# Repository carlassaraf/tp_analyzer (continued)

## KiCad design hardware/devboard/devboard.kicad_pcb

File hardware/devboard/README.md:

# RP2350B Development Board

**Rev 1** — 2026-08-18 · Fabrizio Carlassara · UTN FRA, Departamento de Ingeniería Electrónica, Cátedra de Proyecto Final

KiCad project: [`devboard.kicad_pro`](devboard.kicad_pro) · Schematic: [`devboard.kicad_sch`](devboard.kicad_sch) · PCB: [`devboard.kicad_pcb`](devboard.kicad_pcb)

## Overview

A minimal development/breakout board built around the **[Core2350B0](https://www.waveshare.com/wiki/Core2350B0)** module (an RP2350B‑QFN80 SoM), with a parallel-interface **[3.5″ ILI9486 TFT + SD card shield](https://www.lcdwiki.com/3.5inch_Arduino_Display-UNO)**, a rotary encoder for UI input, 8 analog input headers, an I²C header, an SWD debug header, and a selectable power path that can run from USB, an external 5V source/boost module, or a Li‑Po/Li-ion battery.

- **Board:** 2-layer, 55.45 mm × 64.95 mm
- **MCU module:** U1 — [Core2350B0](https://www.waveshare.com/wiki/Core2350B0) (RP2350B in QFN-80), custom project symbol/footprint
- **Display:** U4 — [ILI9486 3.5″ TFT shield](https://www.lcdwiki.com/3.5inch_Arduino_Display-UNO) (8-bit parallel/8080 interface) with onboard microSD slot (SPI)
- **Power:** Li‑Po/Li‑ion input, USB VBUS, or external 5V/boost module → selectable VSYS → AMS1117-3.3 → +3V3
- **Input:** SW1 rotary encoder with integrated push-button

## Components

| Ref | Part | Function |
|---|---|---|
| U1 | [Core2350B0](https://www.waveshare.com/wiki/Core2350B0) (RP2350B QFN‑80) | Main MCU module |
| U2 | [AMS1117CD‑3.3](https://www.advanced-monolithic.com/pdf/ds1117.pdf) (SOT‑223) | Linear regulator, VSYS → +3V3 |
| U4 | [ILI9486 3.5″ TFT Shield](https://www.lcdwiki.com/3.5inch_Arduino_Display-UNO) | Display + resistive-touch‑shield form factor, 8-bit parallel LCD bus, onboard microSD (SPI) |
| U5 | 3-pin header, socket for [PCBoard.ca Mini Boost Converter 5V](https://www.pcboard.ca/mini-boost-converter-5v) | Plug-in step-up module, boosts VBAT (~3.7V Li‑Po) to a regulated +5V |
| SW1 | Rotary encoder w/ push switch | UI input — quadrature A/B + click |
| R1, R2, R3 | 10 kΩ (0805) | Pull-ups to +3V3 for encoder A, B, and switch lines |
| C1, C5 | 10 µF MLCC | Decoupling on VSYS and +3V3 |
| JP1 | 3-pin jumper (bridged 1‑2 by default) | VSYS power-source select: **+5V** (external header/boost module) vs **VBUS** (USB) |
| J4 | 3-pin header | SWD debug (SWCLK, GND, SWDIO) |
| J5 | 4-pin header | I²C breakout (+3V3, GPIO8, GPIO9, GND) |
| J6–J13 | 2-pin headers | ADC0–ADC7 analog input breakouts (signal + GND) |
| J14 | 2-pin header | Battery input (VBAT, GND) — single-cell Li‑Po/Li‑ion, no onboard charge management |

> ⚠️ U5 and J14 use generic 2.54 mm pin-header footprints as placeholders — U5 is a socket for the plug-in boost module linked above (not a fixed regulator IC on this PCB), and J14 is a bare 2-pin header rather than a JST-PH battery connector. J4 is likewise a standard 2.54 mm SWD header (a schematic note calls it a "JST Debug Connector", but no JST part is actually used).

## Power architecture

```
Battery (Li-Po/Li-ion, ~3.7V) ──► J14 ──► U5 (external boost module) ──► +5V ─┐
                                                                               ├─► JP1 ──► VSYS ──► U2 (AMS1117-3.3) ──► +3V3
                                       USB VBUS (from U1's onboard USB) ──────┘
```

- **JP1** selects what feeds VSYS: bridge pins **1-2** to power VSYS from the external **+5V** rail (boost module output), or bridge **2-3** to power VSYS from USB **VBUS** instead.
- **VSYS** feeds the AMS1117-3.3 (U2), which produces the board's **+3V3** rail for the RP2350B and all logic.
- **VSYS** also feeds the TFT shield's 5V pin directly (U4 pad 19), so the display runs from the ~5V rail while its logic/control lines are driven at 3.3V from the RP2350B GPIOs.
- U1's own **USB_DP/USB_DM** pins are not routed to this board — the Core2350B0 module has its own USB connector; only its **VBUS** pin is brought out here for power-source selection.
- U1's **RUN**, **BOOTSEL**, **3V3_EN**, and **ADC_VREF** pins are also not routed on this board (available on the module for future use — e.g. reset/BOOTSEL buttons, external ADC reference).

## Core2350B0 (RP2350B) pin usage

| GPIO | Net | Connected to | Role |
|---|---|---|---|
| GPIO0 | /GPIO0 | U4 pad 8 (LCD_D0) | TFT parallel data bus |
| GPIO1 | /GPIO1 | U4 pad 7 (LCD_D1) | TFT parallel data bus |
| GPIO2 | /GPIO2 | U4 pad 14 (LCD_D2) | TFT parallel data bus |
| GPIO3 | /GPIO3 | U4 pad 13 (LCD_D3) | TFT parallel data bus |
| GPIO4 | /GPIO4 | U4 pad 12 (LCD_D4) | TFT parallel data bus |
| GPIO5 | /GPIO5 | U4 pad 11 (LCD_D5) | TFT parallel data bus |
| GPIO6 | /GPIO6 | U4 pad 10 (LCD_D6) | TFT parallel data bus |
| GPIO7 | /GPIO7 | U4 pad 9 (LCD_D7) | TFT parallel data bus |
| GPIO8 | /GPIO8 | J5 pad 2 | I²C header (SDA/SCL — function assigned in firmware) |
| GPIO9 | /GPIO9 | J5 pad 3 | I²C header (SDA/SCL — function assigned in firmware) |
| GPIO10 | /GPIO10 | *(none)* | Not routed off-module — reserved/available |
| GPIO11 | /GPIO11 | *(none)* | Not routed off-module — reserved/available |
| GPIO12 | /GPIO12 | U4 pad 4 (SD_D0) | microSD SPI — MISO |
| GPIO13 | /GPIO13 | U4 pad 6 (SD_SS) | microSD SPI — chip select |
| GPIO14 | /GPIO14 | U4 pad 3 (SD_SCK) | microSD SPI — clock |
| GPIO15 | /GPIO15 | U4 pad 5 (SD_DI) | microSD SPI — MOSI |
| GPIO16 | /GPIO16 | U4 pad 23 (LCD_RD) | TFT control — read strobe |
| GPIO17 | /GPIO17 | U4 pad 24 (LCD_WR) | TFT control — write strobe |
| GPIO18 | /GPIO18 | U4 pad 25 (LCD_RS) | TFT control — register/data select |
| GPIO19 | /GPIO19 | U4 pad 26 (LCD_CS) | TFT control — chip select |
| GPIO20 | /GPIO20 | U4 pad 27 (LCD_RST) | TFT control — reset |
| GPIO21–GPIO26 | /GPIO21…/GPIO26 | *(none)* | Not routed off-module — reserved/available |
| GPIO27 | /GPIO27 | R1 (10k → +3V3), SW1 pad A | Rotary encoder — channel A (pulled up) |
| GPIO28 | /GPIO28 | *(none)* | Not routed off-module — reserved/available |
| GPIO29 | /GPIO29 | R2 (10k → +3V3), SW1 pad B | Rotary encoder — channel B (pulled up) |
| GPIO30 | /GPIO30 | R3 (10k → +3V3), SW1 pad S1 | Rotary encoder — push switch (pulled up) |
| GPIO31–GPIO39 | /GPIO31…/GPIO39 | *(none)* | Not routed off-module — reserved/available |
| GPIO40 | /GPIO40_ADC0 | J6 | ADC0 analog input header |
| GPIO41 | /GPIO41_ADC1 | J7 | ADC1 analog input header |
| GPIO42 | /GPIO42_ADC2 | J8 | ADC2 analog input header |
| GPIO43 | /GPIO43_ADC3 | J9 | ADC3 analog input header |
| GPIO44 | /GPIO44_ADC4 | J10 | ADC4 analog input header |
| GPIO45 | /GPIO45_ADC5 | J11 | ADC5 analog input header |
| GPIO46 | /GPIO46_ADC6 | J12 | ADC6 analog input header |
| GPIO47 | /GPIO47_ADC7 | J13 | ADC7 analog input header |
| SWCLK | /SWCLK | J4 pad 1 | SWD debug clock |
| SWDIO | /SWD | J4 pad 3 | SWD debug data |
| VBUS | VBUS | JP1 pad 3 | USB 5V sense/power (module's own USB port) |
| 3V3 | +3V3 | U2 output, C5, R1–R3, J5 pad 1 | Regulated logic supply |
| GND | GND | Board ground | Common ground |
| RUN | *(unconnected)* | — | Reset — not routed on this board |
| BOOTSEL | *(unconnected)* | — | BOOTSEL — not routed on this board |
| 3V3_EN | *(unconnected)* | — | Regulator enable — not routed on this board |
| ADC_VREF | *(unconnected)* | — | External ADC reference — not routed on this board |
| USB_DP / USB_DM | *(unconnected)* | — | USB data — handled by module's onboard USB connector |

## Connector reference

| Connector | Pins | Notes |
|---|---|---|
| J4 (SWD) | 1: SWCLK · 2: GND · 3: SWDIO | Standard 2.54 mm 3-pin debug header |
| J5 (I2C) | 1: +3V3 · 2: GPIO8 · 3: GPIO9 · 4: GND | Pin function (SDA/SCL) set in firmware |
| J6–J13 (ADC0–ADC7) | 1: ADCx signal · 2: GND | One 2-pin header per analog channel |
| J14 (Battery) | 1: VBAT · 2: GND | Single-cell Li‑Po/Li‑ion, no charge management on-board |
| U5 (Boost) | 1: VBAT in · 2: GND · 3: +5V out | Socket for external boost module |
| JP1 (Power select) | 1: +5V · 2: VSYS · 3: VBUS | Bridge 1‑2: power from external +5V/boost; bridge 2‑3: power from USB |

## Open items / things to double check before fabrication

- No charge-management IC for the Li‑Po/Li‑ion battery on J14 — charging must be handled externally.
- Confirm current rating of the boost module against the board's total load (display backlight + MCU) before relying on it.
- GPIO10, 11, 21–26, 28, and 31–39 are unused on this revision — available for future expansion.
- U1's RUN/BOOTSEL are not brought out — flashing relies on the Core2350B0 module's own USB/BOOTSEL, or SWD via J4.

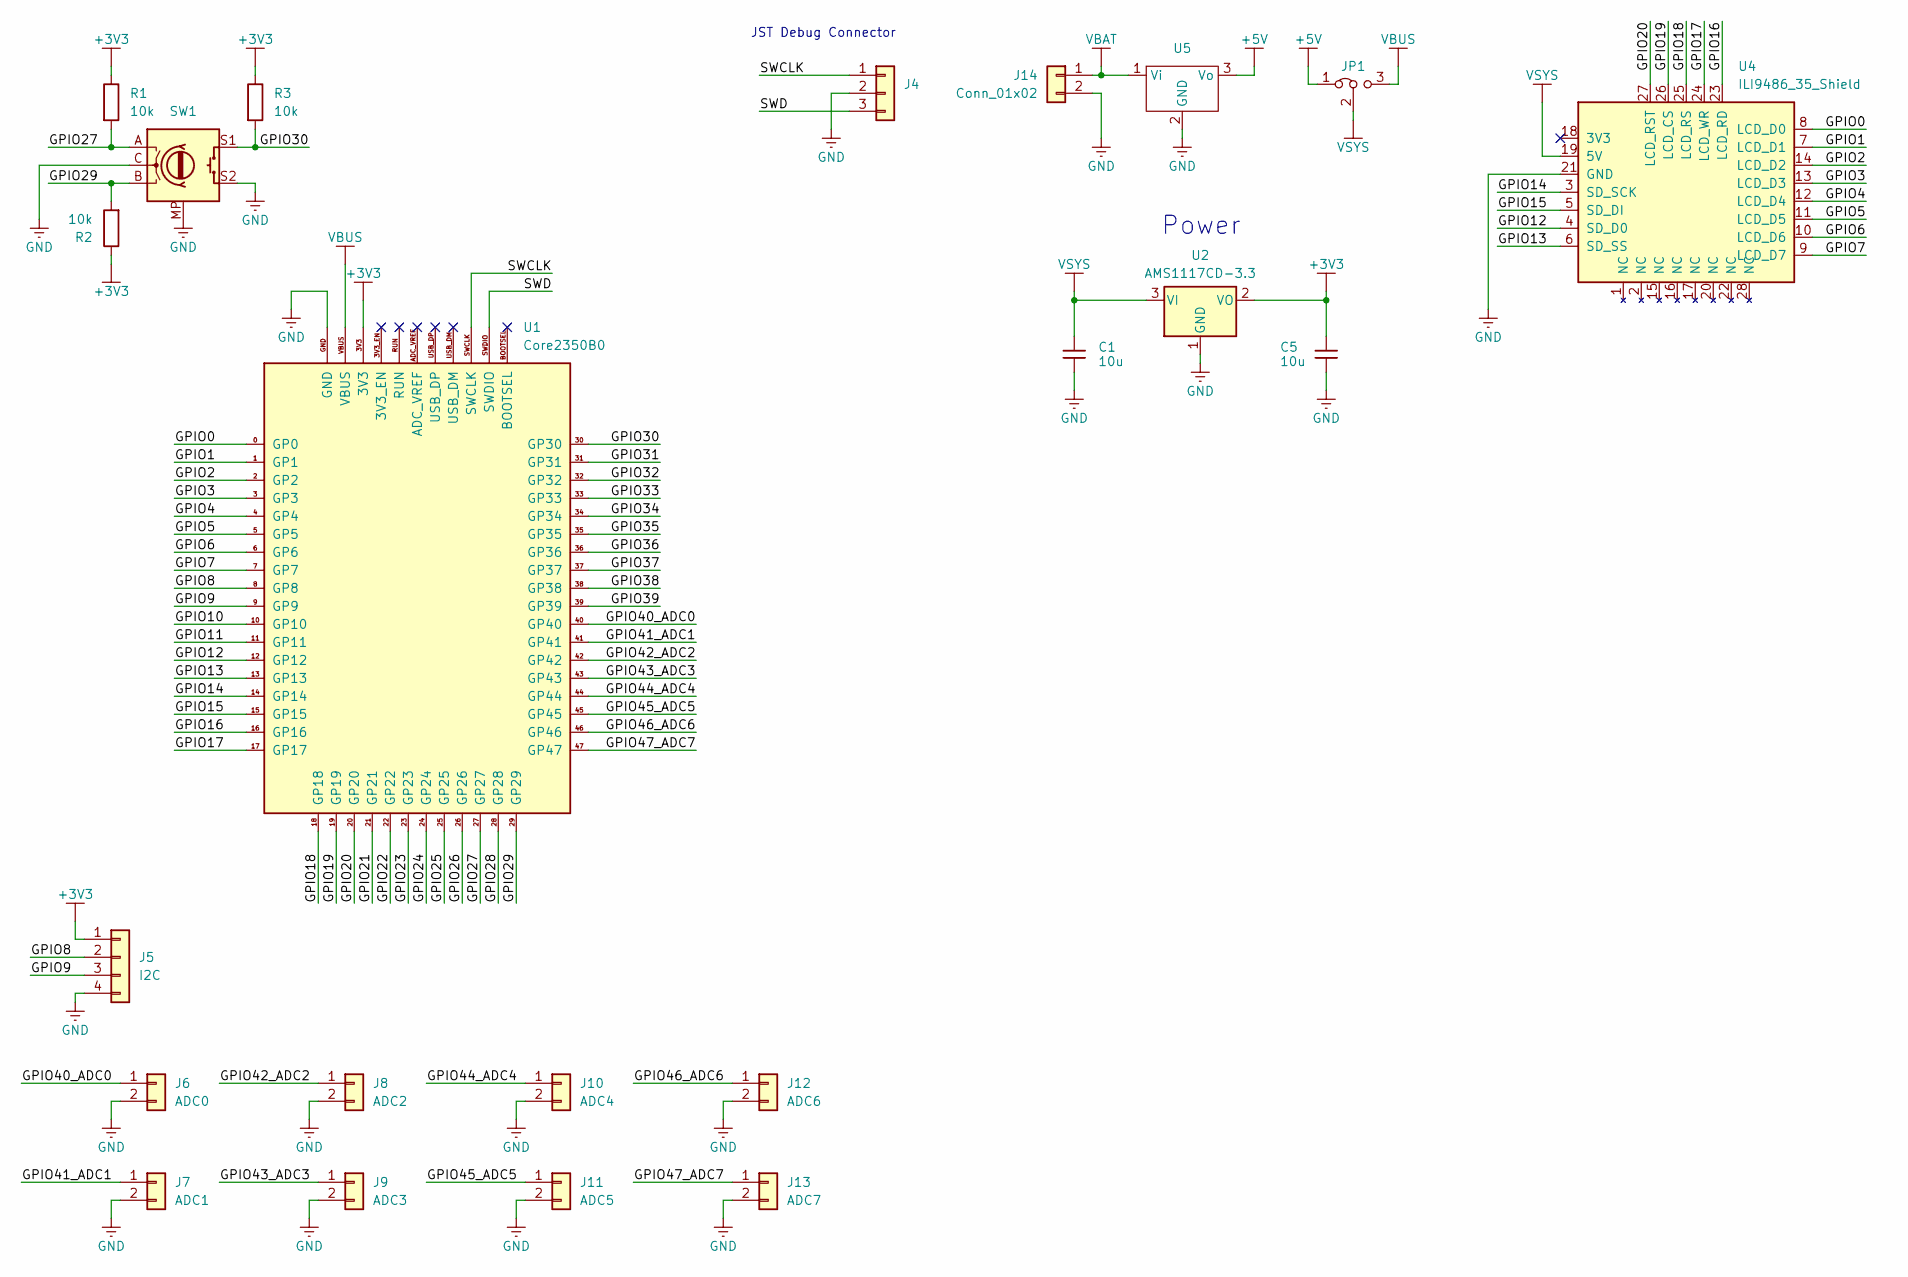
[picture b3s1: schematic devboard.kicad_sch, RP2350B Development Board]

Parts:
C1, C5: 10u; C_0603_1608Metric; voltage 16V; tolerance 10%; part_uid RP-01GYSK-AVBE41
J4: Conn_01x03; PinSocket_1x03_P2.54mm_Vertical
J5: I2C; PinSocket_1x04_P2.54mm_Vertical
J6: ADC0; PinSocket_1x02_P2.54mm_Vertical
J7: ADC1; PinSocket_1x02_P2.54mm_Vertical
J8: ADC2; PinSocket_1x02_P2.54mm_Vertical
J9: ADC3; PinSocket_1x02_P2.54mm_Vertical
J10: ADC4; PinSocket_1x02_P2.54mm_Vertical
J11: ADC5; PinSocket_1x02_P2.54mm_Vertical
J12: ADC6; PinSocket_1x02_P2.54mm_Vertical
J13: ADC7; PinSocket_1x02_P2.54mm_Vertical
J14: Conn_01x02; PinSocket_1x02_P2.54mm_Vertical
JP1: Jumper_3_Bridged12; PinSocket_1x03_P2.54mm_Vertical
R1, R2, R3: 10k; R_0805_2012Metric
SW1: RotaryEncoder_Switch_MP; RotaryEncoder_Alps_EC11E-Switch_Vertical_H20mm
U1: Core2350B0
U2: AMS1117CD-3.3; SOT-223-3_TabPin2
U4: ILI9486_35_Shield
U5: PinHeader_1x03_P2.54mm_Vertical

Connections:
+3V3: C5.1, J5.1, R1.1, R2.1, R3.1, U1.3V3, U2.2 (VO)
+5V: JP1.1 (A), U5.3 (Vo)
/GPIO0: U1.0 (GP0), U4.8 (LCD_D0)
/GPIO1: U1.1 (GP1), U4.7 (LCD_D1)
/GPIO2: U1.2 (GP2), U4.14 (LCD_D2)
/GPIO3: U1.3 (GP3), U4.13 (LCD_D3)
/GPIO4: U1.4 (GP4), U4.12 (LCD_D4)
/GPIO5: U1.5 (GP5), U4.11 (LCD_D5)
/GPIO6: U1.6 (GP6), U4.10 (LCD_D6)
/GPIO7: U1.7 (GP7), U4.9 (LCD_D7)
/GPIO8: J5.2, U1.8 (GP8)
/GPIO9: J5.3, U1.9 (GP9)
/GPIO10: U1.10 (GP10)
/GPIO11: U1.11 (GP11)
/GPIO12: U1.12 (GP12), U4.4 (SD_D0)
/GPIO13: U1.13 (GP13), U4.6 (SD_SS)
/GPIO14: U1.14 (GP14), U4.3 (SD_SCK)
/GPIO15: U1.15 (GP15), U4.5 (SD_DI)
/GPIO16: U1.16 (GP16), U4.23 (LCD_RD)
/GPIO17: U1.17 (GP17), U4.24 (LCD_WR)
/GPIO18: U1.18 (GP18), U4.25 (LCD_RS)
/GPIO19: U1.19 (GP19), U4.26 (LCD_CS)
/GPIO20: U1.20 (GP20), U4.27 (LCD_RST)
/GPIO21: U1.21 (GP21)
/GPIO22: U1.22 (GP22)
/GPIO23: U1.23 (GP23)
/GPIO24: U1.24 (GP24)
/GPIO25: U1.25 (GP25)
/GPIO26: U1.26 (GP26)
/GPIO27: R1.2, SW1.A, U1.27 (GP27)
/GPIO28: U1.28 (GP28)
/GPIO29: R2.2, SW1.B, U1.29 (GP29)
/GPIO30: R3.2, SW1.S1, U1.30 (GP30)
/GPIO31: U1.31 (GP31)
/GPIO32: U1.32 (GP32)
/GPIO33: U1.33 (GP33)
/GPIO34: U1.34 (GP34)
/GPIO35: U1.35 (GP35)
/GPIO36: U1.36 (GP36)
/GPIO37: U1.37 (GP37)
/GPIO38: U1.38 (GP38)
/GPIO39: U1.39 (GP39)
/GPIO40_ADC0: J6.1, U1.40 (GP40)
/GPIO41_ADC1: J7.1, U1.41 (GP41)
/GPIO42_ADC2: J8.1, U1.42 (GP42)
/GPIO43_ADC3: J9.1, U1.43 (GP43)
/GPIO44_ADC4: J10.1, U1.44 (GP44)
/GPIO45_ADC5: J11.1, U1.45 (GP45)
/GPIO46_ADC6: J12.1, U1.46 (GP46)
/GPIO47_ADC7: J13.1, U1.47 (GP47)
/SWCLK: J4.1, U1.SWCLK
/SWD: J4.3, U1.SWDIO
GND: C1.2, C5.2, J4.2, J5.4, J6.2, J7.2, J8.2, J9.2, J10.2, J11.2, J12.2, J13.2, J14.2, SW1.C, SW1.MP, SW1.S2, U1.GND, U2.1 (GND), U4.21 (GND), U5.2 (GND)
VBAT: J14.1, U5.1 (Vi)
VBUS: JP1.3 (B), U1.VBUS
VSYS: C1.1, JP1.2 (C), U2.3 (VI), U4.19 (5V)

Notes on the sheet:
JST Debug Connector
Power

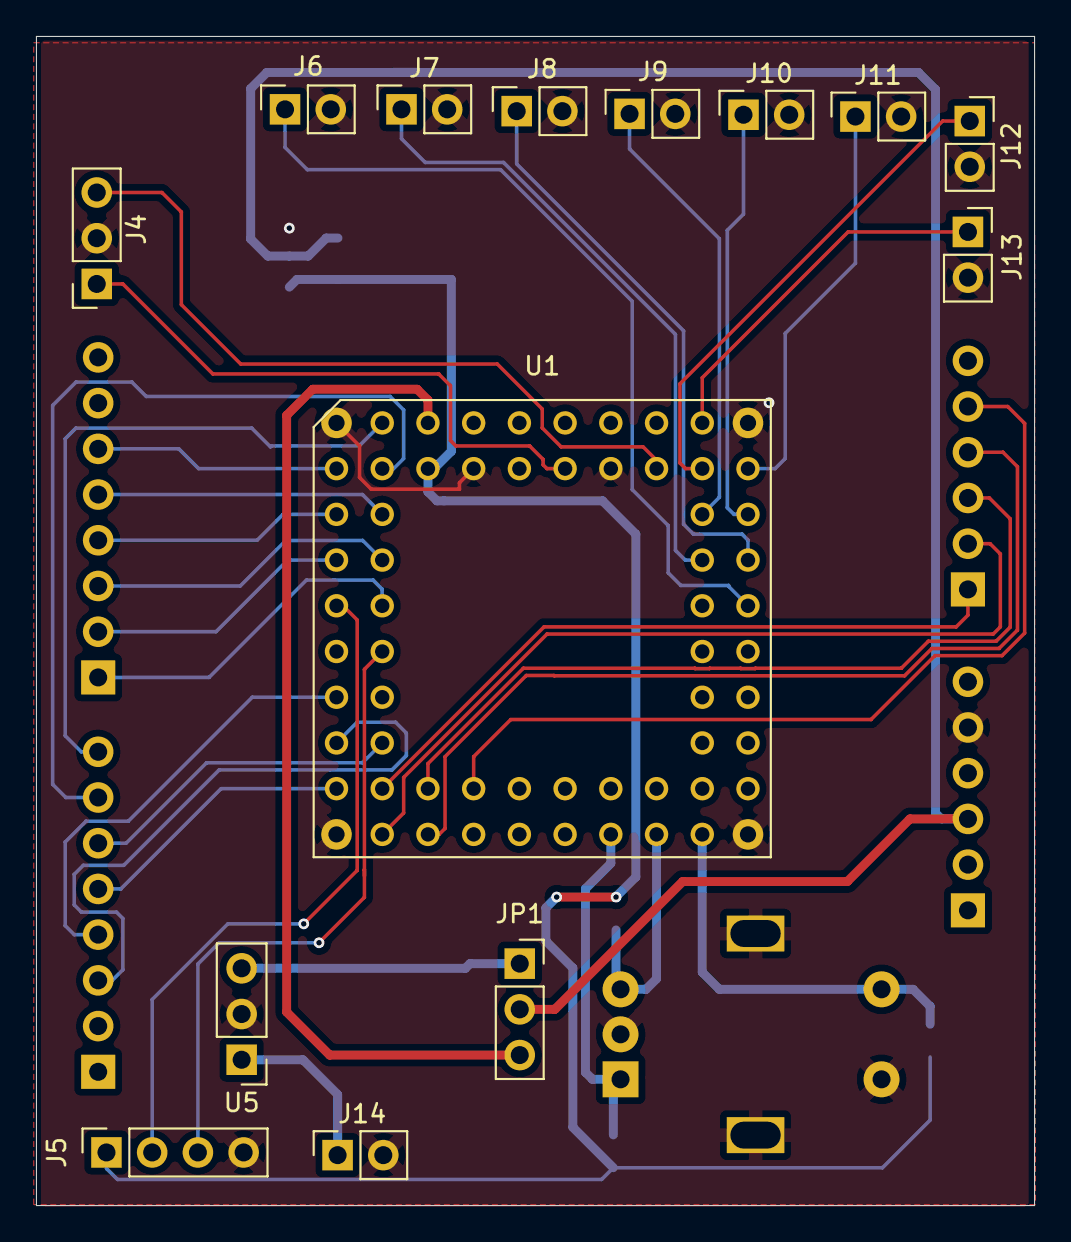
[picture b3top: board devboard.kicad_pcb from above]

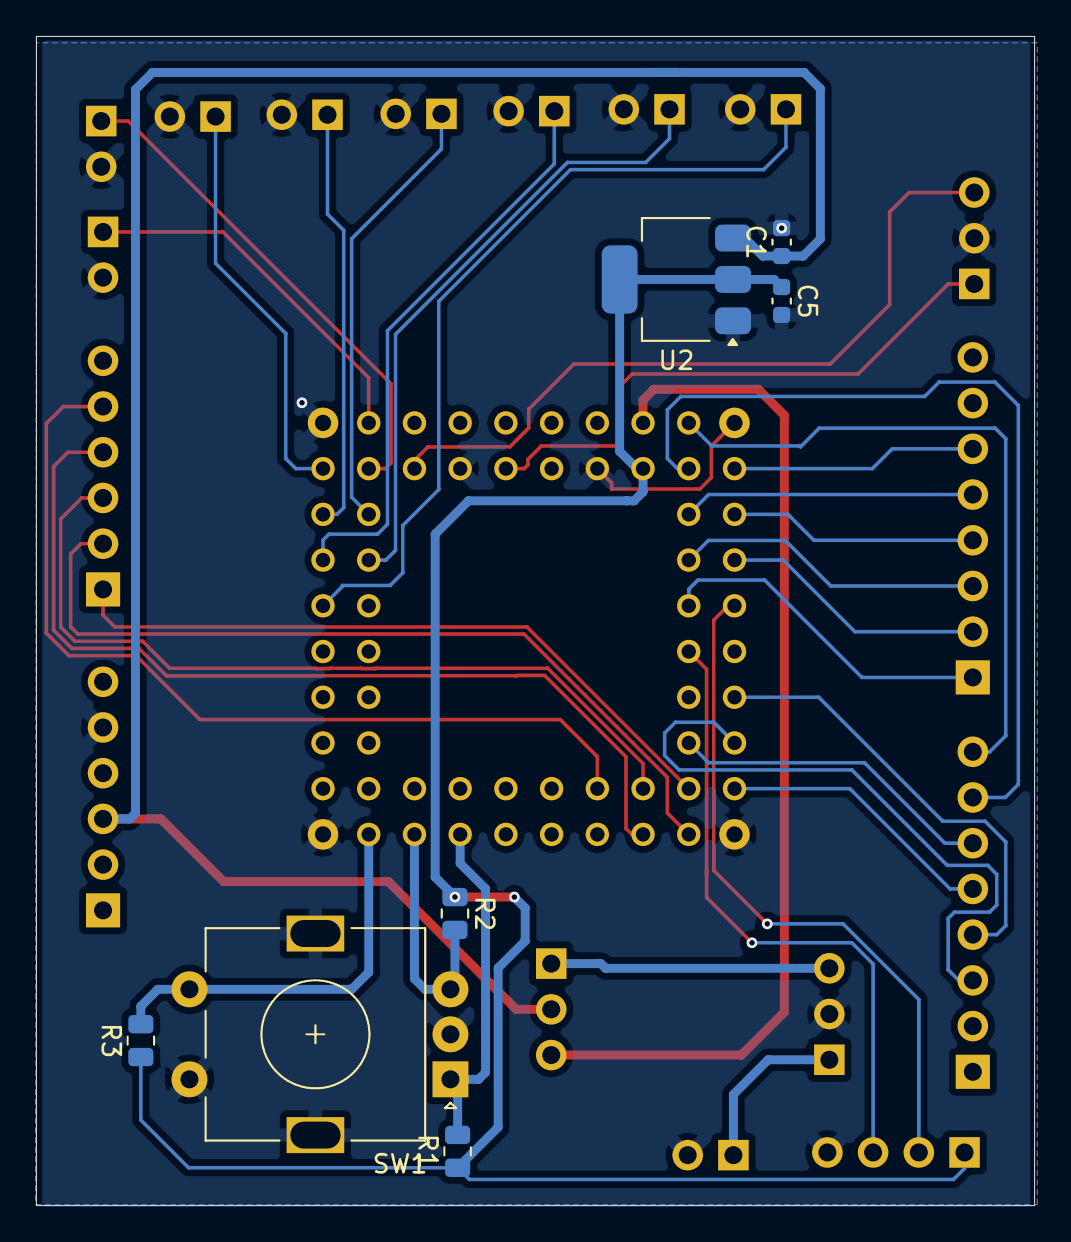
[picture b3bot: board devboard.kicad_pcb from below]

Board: 2 copper layers, 55.5 x 64.9 mm, 22 parts (7 on the bottom side), 38 nets.

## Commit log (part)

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2026-04-25 feat: basic hello world from lvgl
2026-04-26 fix: inverted color by default
2026-04-26 fix: wire freertos tick to lvgl tick
2026-04-26 feat: add boot screen
2026-04-26 feat: add encoder support
2026-04-27 feat: add hal gpio functions for parallel writing
2026-04-27 feat: add ili9486 display support
2026-04-27 feat: hal for ADC
2026-04-27 feat: add adc task with isr for dma
2026-04-27 feat: provide function to update chart data
2026-04-27 test: tentative adc definitions
2026-04-29 feat: basic squareline initial project
2026-04-29 chore: move ui directory
2026-05-04 chore: move firmware directory
2026-05-05 fix: update pinout for pcb prototype
2026-05-15 fix: revert inverted colors
2026-05-15 feat: squareline export
2026-05-16 feat: basic plot ui
2026-05-29 perf: change gpio mask writing for PIO + DMA
2026-05-29 perf: move pio and dma to a hal
2026-06-05 fix: adjust scaling
2026-06-05 feat: add lvgl submodule
2026-06-09 feat: squareline design
2026-06-09 feat: add ui for home and fft chart
2026-06-09 fix: click events from menu
2026-06-09 feat: add fft and menu screen managers
2026-06-10 feat: add cmsis support
2026-06-10 feat: link cmsis dsp wrapper
2026-06-10 feat: fft update from adc sampling
2026-06-10 feat: update fft chart and scroll bins with encoder
2026-06-10 fix: handle screen transitions from events
2026-06-10 style: hide data point markers
2026-06-10 feat: fft x ticks scroll with encoder
2026-06-15 style: manage theme colors
2026-06-15 style: create new fonts from IBM Mono and IBM Sans
2026-06-15 style: add icons
2026-06-15 feat: manage top bar as a common component
2026-06-15 feat: update boot and menu to a more modern ui
2026-06-15 fix: update font paths
2026-06-15 feat: change plotter screen to oscilloscope screen with updated UI
2026-06-15 style: add oscilloscope card default state as focused
2026-06-15 fix: update real time drawing
2026-06-15 feat: add side menu to oscilloscope screen
2026-06-15 feat: add menu side bar in oscilloscope screen
2026-06-15 fix: reserve more memory for lvgl
2026-06-15 fix: downgrade PIO clock speed
2026-06-15 feat: handle signal switching
2026-06-15 feat: handle submenus in the oscilloscope screen
2026-06-15 feat: update vertical scales and keep track of the last selected
2026-06-15 feat: update time scales in the UI on encoder interaction
2026-06-15 feat: update value labels from oscilloscope with ADC data
2026-06-15 feat: add support for float data in labels
2026-06-15 fix: show actual absolute values
2026-06-16 fix: update unit in chart
2026-06-16 feat: update FFT screen
2026-06-16 perf: minimize memory usage
2026-06-16 feat: add settings and datetime screens
2026-06-16 chore: remove legacy fonts
2026-06-16 fix: add more heap to LVGL
2026-06-16 fix: add missing events to transition screen
2026-06-16 fix: add event trickle
2026-06-16 perf: lazy load screens to avoid heap peak consumption all at once
2026-06-16 fix: guard update commands if screen is not active
2026-06-16 perf: lazy destroy screens to avoid heap extreme usage
2026-06-16 feat: make datetime fields in the UI editable
2026-06-17 chore: tweak top bar component and update name across all screens
2026-06-17 feat: rtc abstraction layer
2026-06-17 feat: add update command for datetime
2026-06-17 fix: update screen update command names
2026-06-17 feat: add component helper to update topbar datetime labels
2026-06-17 feat: let screen manager to update clock on topbar on screen transition and on command
2026-06-17 feat: update datetime preview label in menu context
2026-06-17 feat: update datetime from RAM and add update function
2026-06-17 feat: initialize rtc and hold timer to update every minute
2026-06-17 fix: remove rtc month offset
2026-06-17 feat: modify datetime and RTC with save button and restore labels when leaving screen
2026-06-17 perf: reduce LVGL heap to half to free RAM
2026-06-20 chore(ui): SquareLine Studio minor update
2026-06-20 fix(fft): refresh chart on update and avoid overflowing the 414 px wide chart
2026-06-20 perf(indev): use encoder difference rather than last activity time
2026-06-20 feat(fft): update frquency, peak and rms values via screen_update command in FFT screen
2026-06-20 fix(osc): use real FFT output length to find max amplitude bin
2026-06-20 perf(update): discard repeated update commands to always run the last one
2026-06-20 style(label): move unit label in peak field to allow single decimal values to display without overlapping
2026-06-20 chore(comment): update old comment about clock frequency
2026-06-20 perf(display): add DMA to display flush to remove blocking operation
2026-06-20 perf(indev): increase encoder timer speed to read more frequently
2026-06-20 perf(ui-task): reduce blocking time in UI task
2026-06-20 feat(dma): add completition irq for display
2026-06-20 perf(sampling): halve ADC samples
2026-06-20 feat(ui): add information screen from SquareLine Studio
2026-06-20 fix(ui): match top bar naming convention
2026-06-20 feat(ui): add information screen with an uptime label
